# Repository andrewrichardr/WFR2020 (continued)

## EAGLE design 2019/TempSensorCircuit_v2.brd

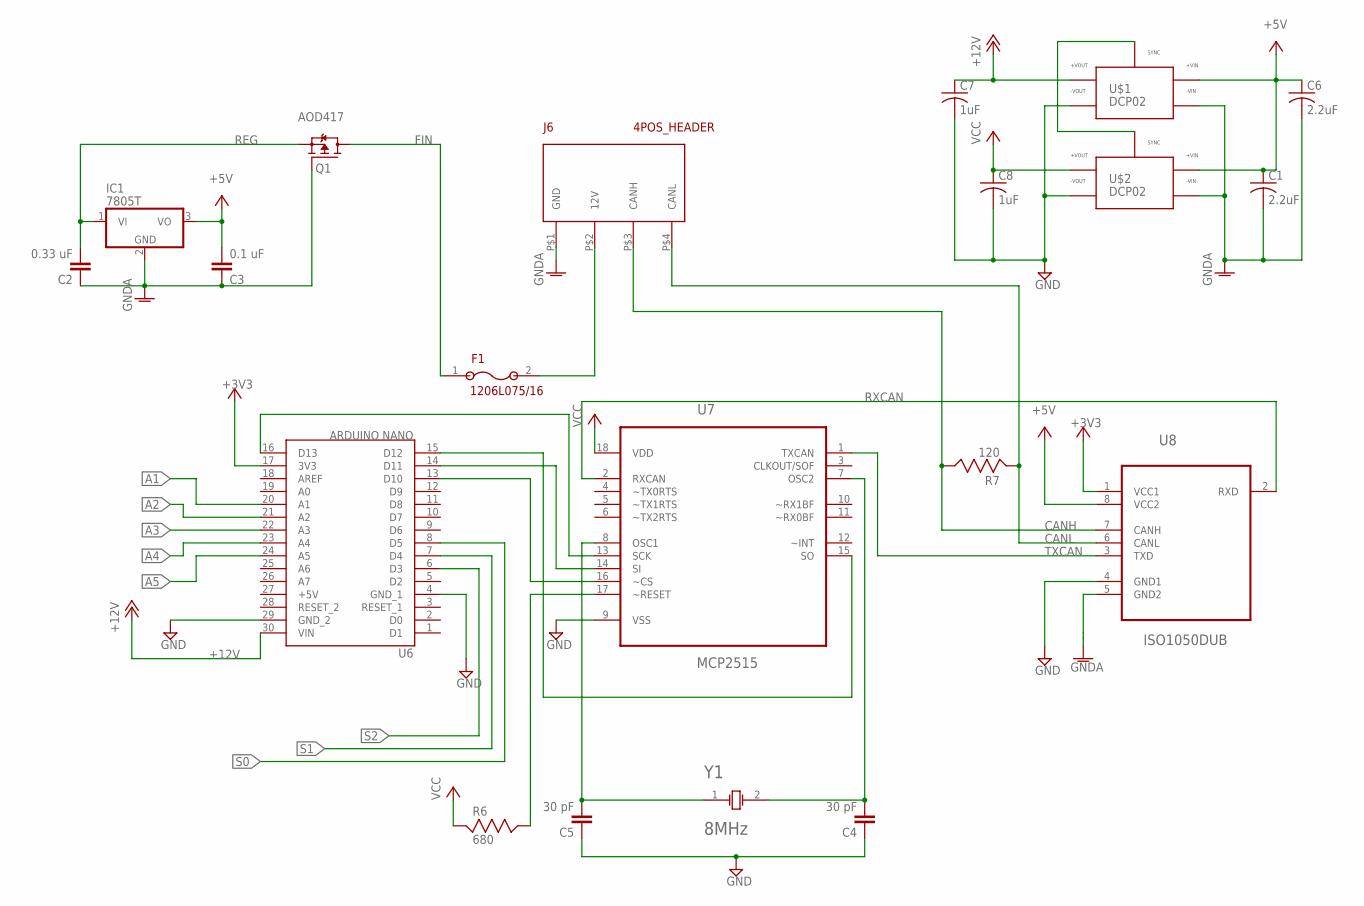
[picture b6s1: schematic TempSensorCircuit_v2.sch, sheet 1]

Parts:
C1, C6: 2.2uF; C0805
C2: 0.33 uF; C5B2.5
C3: 0.1 uF; C5B2.5
C4, C5: 30 pF; C5B2.5
C7, C8: 1uF; C0805
F1: 1206L075/16
IC1: 7805T; TO220H
J6: 4POS_HEADER
Q1: AOD417; TO252
R6: 680; RESC2012X60
R7: 120; RESC2012X60
U6: ARDUINO NANO; NANO
U7: MCP2515; DIP254P762X432-18
U8: ISO1050DUB; SOP254P1040X485-8N
U$1, U$2: DCP02; DIL14
Y1: 8MHz; XTAL_HC49P488W43L1135T465H360

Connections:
+3V3: U6.17 (3V3), U8.1 (VCC1)
+5V: C1.1, C3.2, C6.1, IC1.3 (VO), U6.27 (+5V), U8.8 (VCC2), U$1.1 (+VIN), U$2.1 (+VIN)
+12V: C7.1, U6.30 (VIN), U$1.6 (+VOUT)
A1: U6.20 (A1); also elsewhere on the board
A2: U6.21 (A2); also elsewhere on the board
A3: U6.22 (A3); also elsewhere on the board
A4: U6.23 (A4); also elsewhere on the board
A5: U6.24 (A5); also elsewhere on the board
CANH: J6.P$3 (CANH), R7.2, U8.7 (CANH)
CANL: J6.P$4 (CANL), R7.1, U8.6 (CANL)
FIN: F1.1, Q1.3 (D)
GND: C4.1, C5.1, C7.2, C8.2, U6.4 (GND_1), U6.29 (GND_2), U7.9 (VSS), U8.4 (GND1), U$1.5 (-VOUT), U$2.5 (-VOUT); also elsewhere on the board
GNDA: C1.2, C2.1, C3.1, C6.2, IC1.2 (GND), J6.P$1 (GND), Q1.1 (G), U8.5 (GND2), U$1.2 (-VIN), U$2.2 (-VIN)
unnamed: R6.2, U7.17 (~RESET)
unnamed: U6.16 (D13), U7.13 (SCK)
unnamed: U6.14 (D11), U7.14 (SI)
unnamed: U6.15 (D12), U7.15 (SO)
unnamed: U6.13 (D10), U7.16 (~CS)
unnamed: U$1.14 (SYNC), U$2.14 (SYNC)
unnamed: F1.2, J6.P$2 (12V)
OSC_N: C5.2, U7.8 (OSC1), Y1.1
OSC_P: C4.2, U7.7 (OSC2), Y1.2
REG: C2.2, IC1.1 (VI), Q1.2 (S)
RXCAN: U7.2 (RXCAN), U8.2 (RXD)
S0: U6.8 (D5); also elsewhere on the board
S1: U6.7 (D4); also elsewhere on the board
S2: U6.6 (D3); also elsewhere on the board
TXCAN: U7.1 (TXCAN), U8.3 (TXD)
VCC: C8.1, R6.1, U7.18 (VDD), U$2.6 (+VOUT); also elsewhere on the board

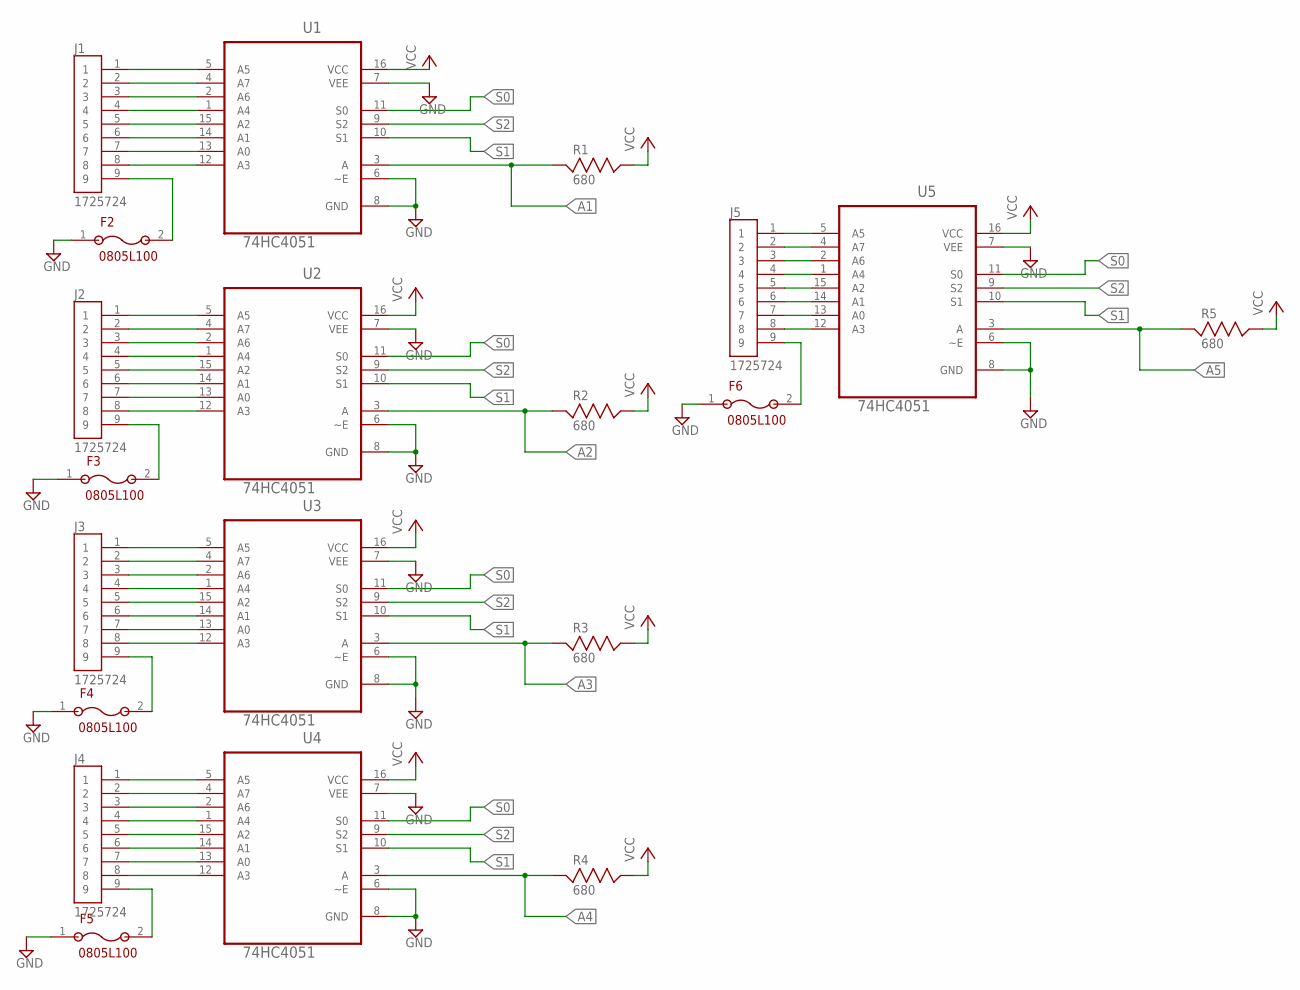
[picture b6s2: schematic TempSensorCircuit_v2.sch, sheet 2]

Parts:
F2, F3, F4, F5, F6: 0805L100; 2012
J1, J2, J3, J4, J5: 1725724; HDRV9W90P254_9X1_2332X620X850
R1, R2, R3, R4, R5: 680; RESC2012X60
U1, U2, U3, U4, U5: 74HC4051; DIP254P762X508-16

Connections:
A1: R1.1, U1.3 (A); also elsewhere on the board
A2: R2.1, U2.3 (A); also elsewhere on the board
A3: R3.1, U3.3 (A); also elsewhere on the board
A4: R4.1, U4.3 (A); also elsewhere on the board
A5: R5.1, U5.3 (A); also elsewhere on the board
GND: F2.1, F3.1, F4.1, F5.1, F6.1, U1.6 (~E), U1.7 (VEE), U1.8 (GND), U2.6 (~E), U2.7 (VEE), U2.8 (GND), U3.6 (~E), U3.7 (VEE), U3.8 (GND), U4.6 (~E), U4.7 (VEE), U4.8 (GND), U5.6 (~E), U5.7 (VEE), U5.8 (GND); also elsewhere on the board
unnamed: J3.1, U3.5 (A5)
unnamed: J3.2, U3.4 (A7)
unnamed: J1.8, U1.12 (A3)
unnamed: J3.3, U3.2 (A6)
unnamed: J3.4, U3.1 (A4)
unnamed: J3.5, U3.15 (A2)
unnamed: J3.6, U3.14 (A1)
unnamed: J3.7, U3.13 (A0)
unnamed: J1.7, U1.13 (A0)
unnamed: J1.6, U1.14 (A1)
unnamed: J1.5, U1.15 (A2)
unnamed: J1.4, U1.1 (A4)
unnamed: J1.3, U1.2 (A6)
unnamed: J1.2, U1.4 (A7)
unnamed: J1.1, U1.5 (A5)
unnamed: J3.8, U3.12 (A3)
unnamed: J2.1, U2.5 (A5)
unnamed: J2.2, U2.4 (A7)
unnamed: J2.3, U2.2 (A6)
unnamed: J2.4, U2.1 (A4)
unnamed: J2.5, U2.15 (A2)
unnamed: J2.6, U2.14 (A1)
unnamed: J2.7, U2.13 (A0)
unnamed: J2.8, U2.12 (A3)
unnamed: J4.1, U4.5 (A5)
unnamed: J4.2, U4.4 (A7)
unnamed: J4.3, U4.2 (A6)
unnamed: J4.4, U4.1 (A4)
unnamed: J4.5, U4.15 (A2)
unnamed: J4.6, U4.14 (A1)
unnamed: J4.7, U4.13 (A0)
unnamed: J4.8, U4.12 (A3)
unnamed: F2.2, J1.9
unnamed: F5.2, J4.9
unnamed: F4.2, J3.9
unnamed: F3.2, J2.9
unnamed: F6.2, J5.9
unnamed: J5.1, U5.5 (A5)
unnamed: J5.2, U5.4 (A7)
unnamed: J5.3, U5.2 (A6)
unnamed: J5.4, U5.1 (A4)
unnamed: J5.5, U5.15 (A2)
unnamed: J5.6, U5.14 (A1)
unnamed: J5.7, U5.13 (A0)
unnamed: J5.8, U5.12 (A3)
S0: U1.11 (S0), U2.11 (S0), U3.11 (S0), U4.11 (S0), U5.11 (S0); also elsewhere on the board
S1: U1.10 (S1), U2.10 (S1), U3.10 (S1), U4.10 (S1), U5.10 (S1); also elsewhere on the board
S2: U1.9 (S2), U2.9 (S2), U3.9 (S2), U4.9 (S2), U5.9 (S2); also elsewhere on the board
VCC: R1.2, R2.2, R3.2, R4.2, R5.2, U1.16 (VCC), U2.16 (VCC), U3.16 (VCC), U4.16 (VCC), U5.16 (VCC); also elsewhere on the board

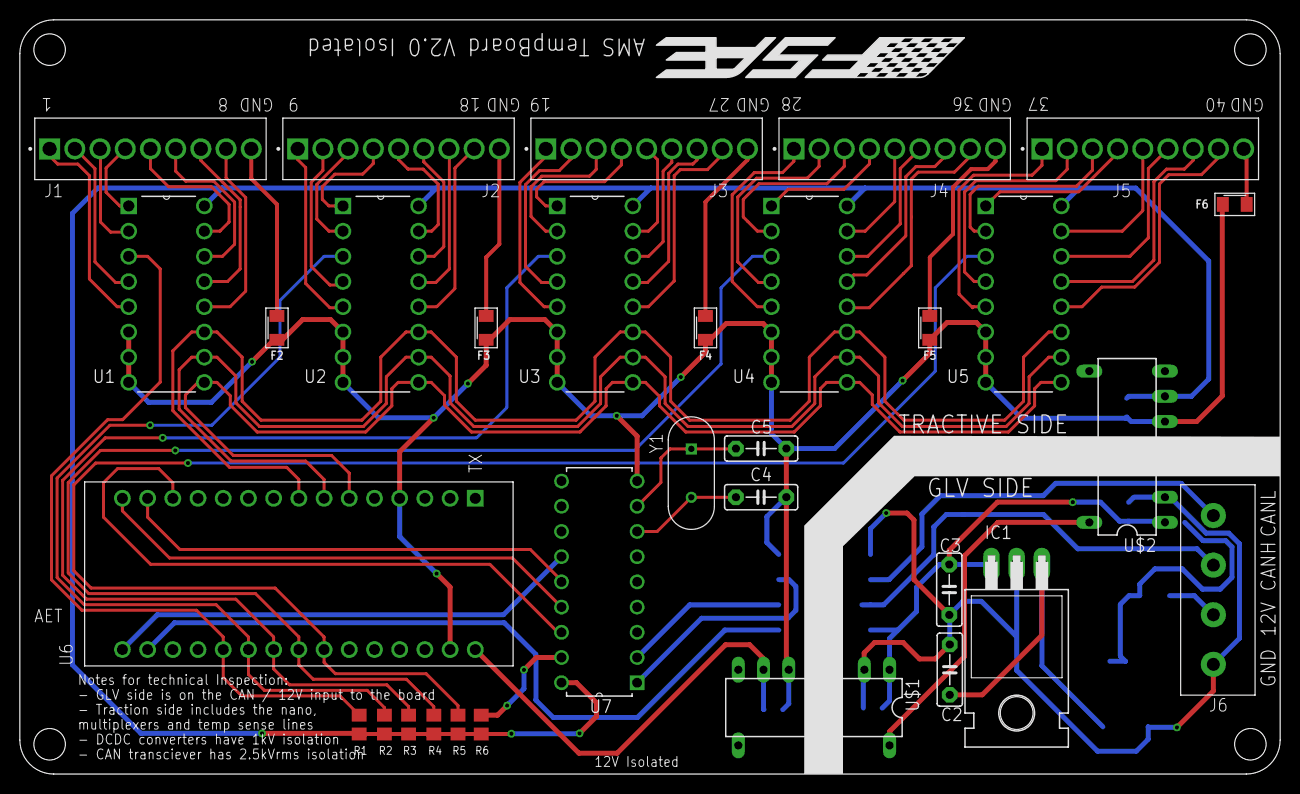
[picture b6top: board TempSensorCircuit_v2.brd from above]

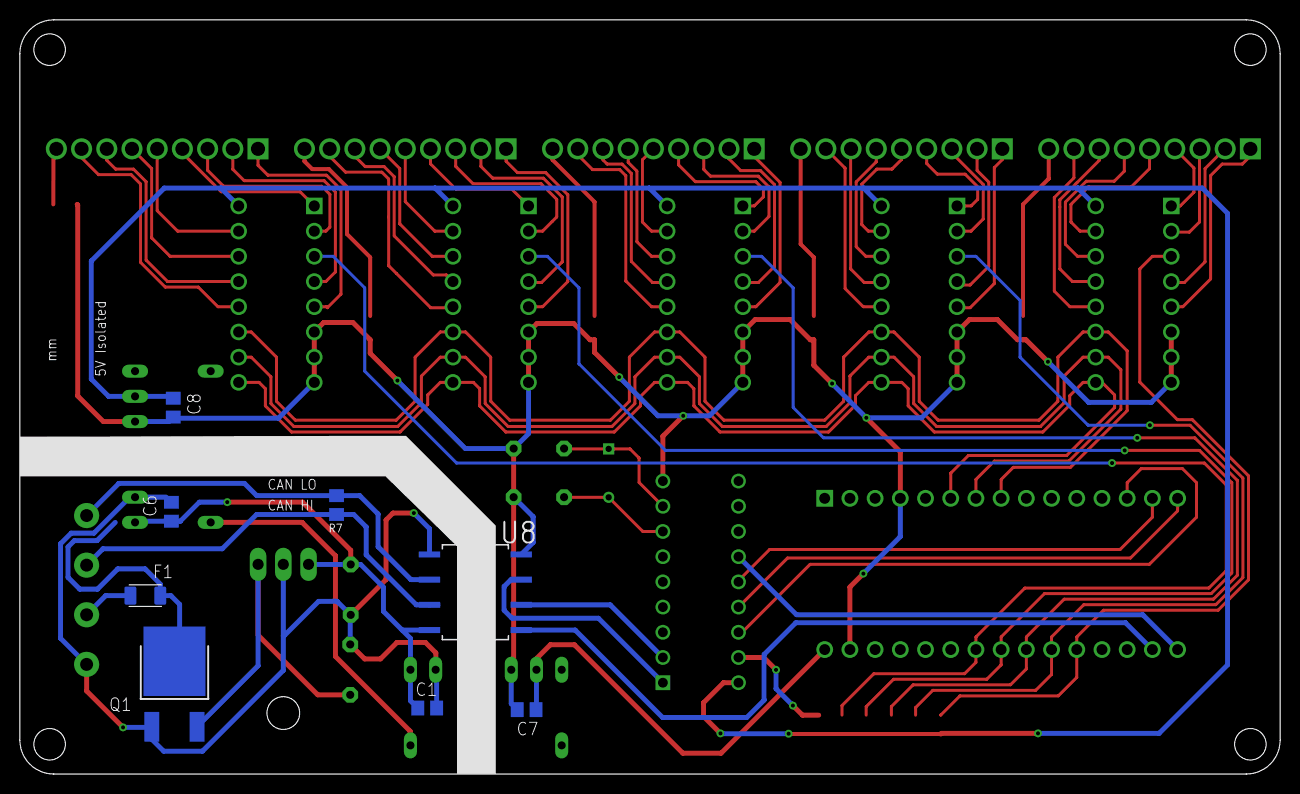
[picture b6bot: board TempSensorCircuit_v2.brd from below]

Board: 2 copper layers, 127.0 x 76.0 mm, 40 parts (8 on the bottom side), 74 nets.

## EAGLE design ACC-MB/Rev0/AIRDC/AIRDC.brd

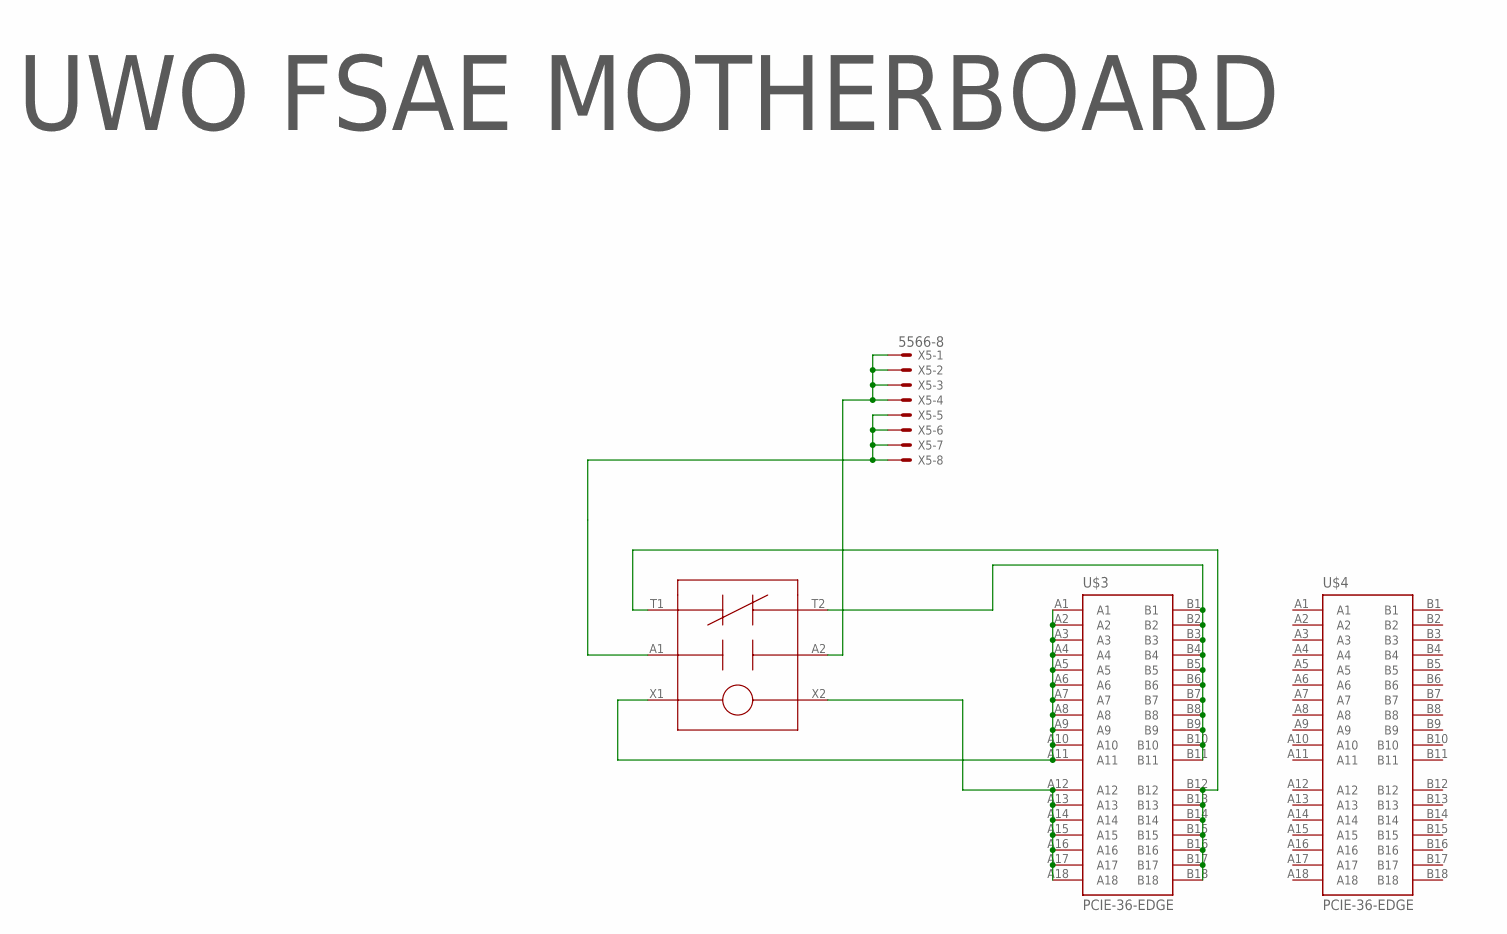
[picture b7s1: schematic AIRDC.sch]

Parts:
U$1: GV224
U$3, U$4: PCIE-36-EDGE; PCI-E_SLOT_36
X5: 5566-8

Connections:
unnamed: U$1.T1, U$3.B12, U$3.B13, U$3.B14, U$3.B15, U$3.B16, U$3.B17, U$3.B18
unnamed: U$1.X1, U$3.A1, U$3.A2, U$3.A3, U$3.A4, U$3.A5, U$3.A6, U$3.A7, U$3.A8, U$3.A9, U$3.A10, U$3.A11
unnamed: U$1.X2, U$3.A12, U$3.A13, U$3.A14, U$3.A15, U$3.A16, U$3.A17, U$3.A18
unnamed: U$1.A1, X5.5, X5.6, X5.7, X5.8
unnamed: U$1.A2, X5.1, X5.2, X5.3, X5.4
unnamed: U$1.T2, U$3.B1, U$3.B2, U$3.B3, U$3.B4, U$3.B5, U$3.B6, U$3.B7, U$3.B8, U$3.B9, U$3.B10, U$3.B11

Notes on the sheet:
UWO FSAE MOTHERBOARD

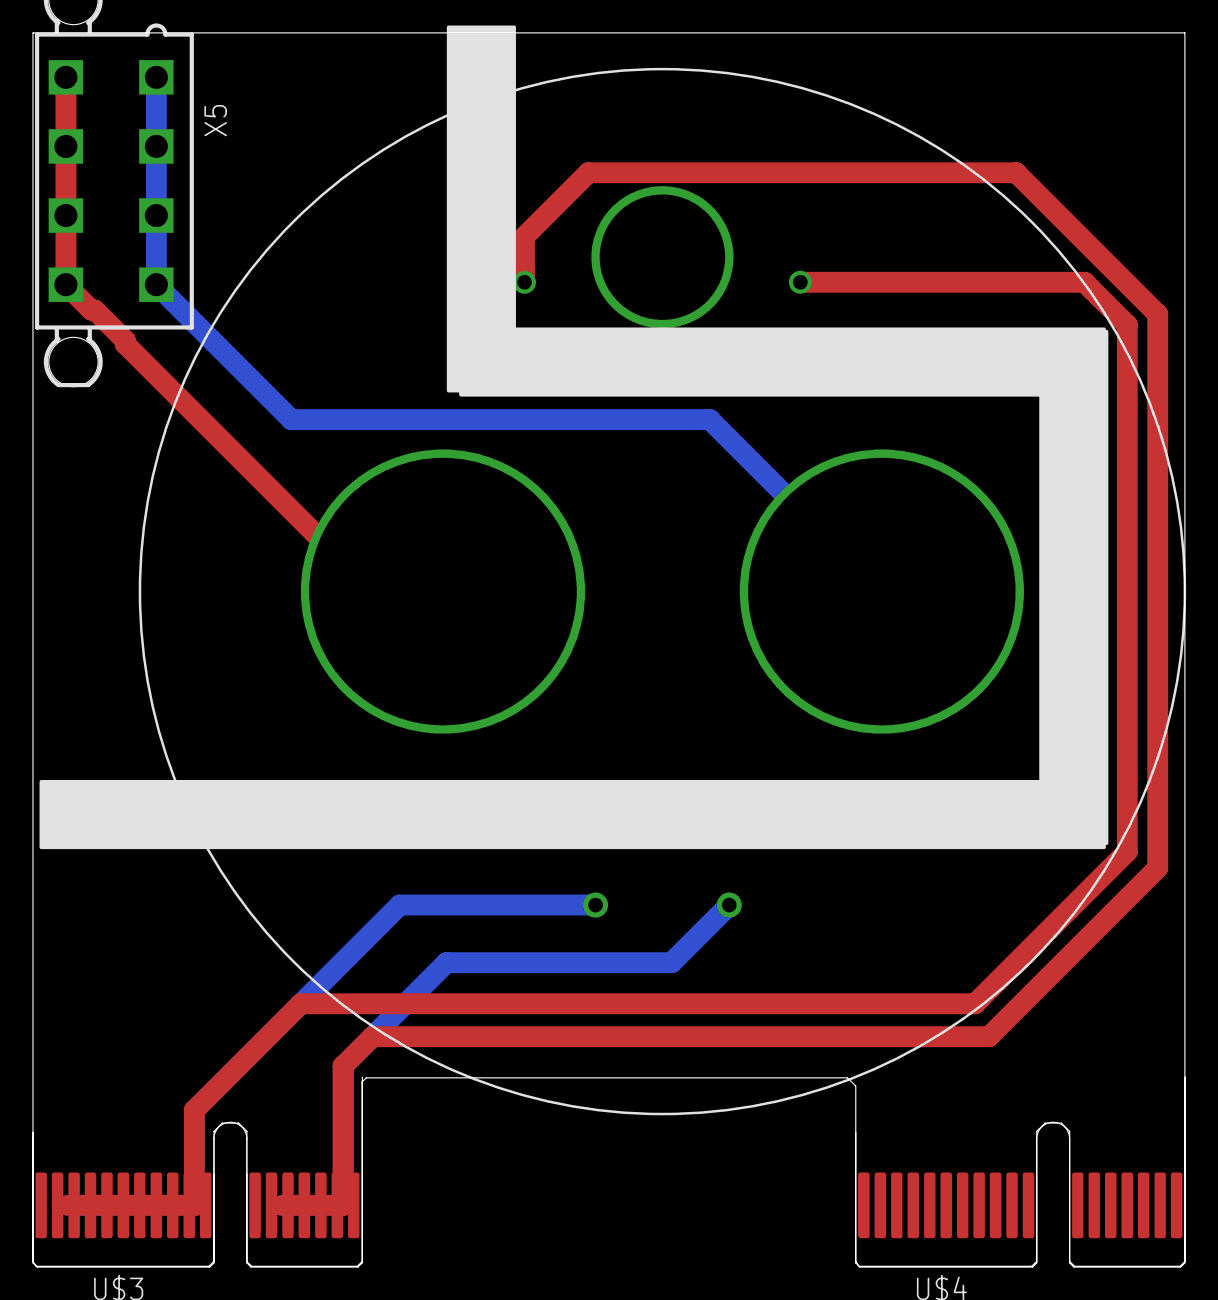
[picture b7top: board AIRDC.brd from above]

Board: 2 copper layers, 70.0 x 75.0 mm, 4 parts (0 on the bottom side), 6 nets.
